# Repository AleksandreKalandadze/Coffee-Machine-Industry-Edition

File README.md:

# Coffee-Machine-Industry-Edition
Coffee Machine Industry Edition

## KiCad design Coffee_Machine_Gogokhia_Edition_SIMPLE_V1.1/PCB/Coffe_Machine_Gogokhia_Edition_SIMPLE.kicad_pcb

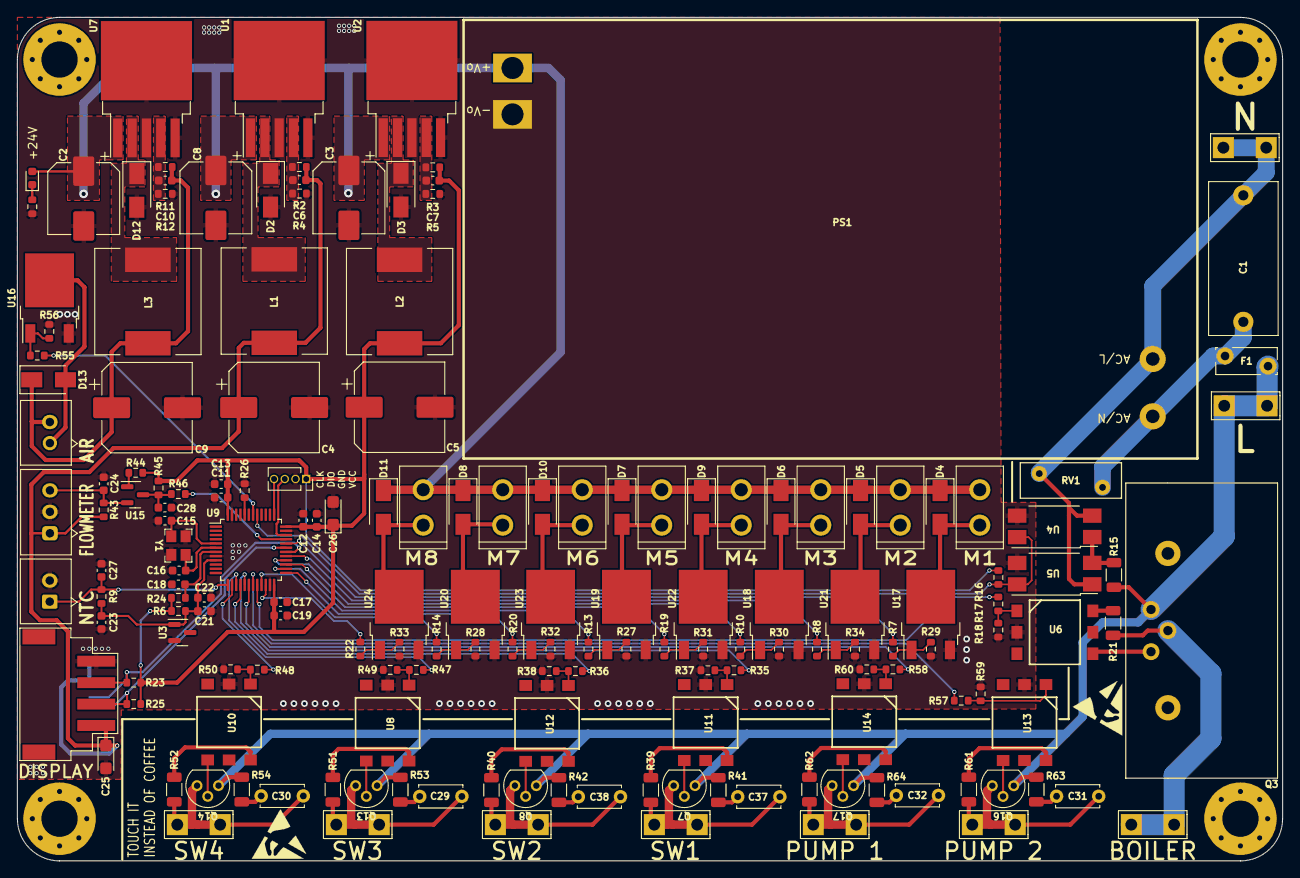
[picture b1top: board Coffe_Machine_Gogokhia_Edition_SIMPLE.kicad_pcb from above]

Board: 2 copper layers, 150.0 x 100.0 mm, 171 parts (1 on the bottom side), 99 nets.

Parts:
C1: 0.22uF; C_Rect_L18.0mm_W8.0mm_P15.00mm_FKS3_FKP3
C2, C3, C8: 100uF; CP_Elec_8x10
C4, C5, C9: 1000uF; CP_Elec_10x10.5
C6, C7, C10: 15nF; C_0603_1608Metric
C11, C13, C17, C18, C21, C22: .1uF; C_0603_1608Metric
C12, C14, C19, C23, C27: .01uF; C_0603_1608Metric
C15, C16: 22pF; C_0603_1608Metric
C24, C28: 0.1uF; C_0603_1608Metric
C25, C26: 100uF; CP_EIA-3216-10_Kemet-I
C29, C30, C31, C32, C37, C38: .01uF; C_Disc_D5.0mm_W2.5mm_P5.00mm
D1: LED; LED_0603_1608Metric
D2, D3, D12: SS34; D_SMA
D4, D5, D6, D7, D8, D9, D10, D11, D13: D; D_SMA
F1: Fuse; Fuse_Bourns_MF-RG300
J1: NEUT_TAB; TAB_Conn
J2: LINE_TAB; TAB_Conn
J3, J4, J6, J8, J10, J13, J16, J17: Conn_01x02; Molex_White_4_2mm_2P
J5: NTC; JST_2.54_2P
J7: JST_3P_2.54mm; JST_2.54_3P
J9: BOILER_TAB; TAB_Conn
J11: SW; PinSocket_1x04_P1.27mm_Vertical
J12: SW3_TAB; TAB_Conn
J14: SW1_TAB; TAB_Conn
J15: SW2_TAB; TAB_Conn
J18: Conn_01x10; FCC_1.0mm_10P
J19: SW; XH2.54_4P_SMD
J20: SW4_TAB; TAB_Conn
J21: Conn_01x02; JST_2.54_2P
J22: PUMP1_TAB; TAB_Conn
J23: PUMP2_TAB; TAB_Conn
L1, L2, L3: 47uH; L_12x12mm_H8mm
PS1: HLK-PM01; IRM-90-24
Q3: BTA16; BTA16_wH_SINK
Q7, Q8, Q13, Q14, Q16, Q17: BT131
R1: 4.1K; R_0603_1608Metric
R2: 3K; R_0603_1608Metric
R3: 1.6K; R_0603_1608Metric
R4, R5, R7, R8, R10, R13, R14, R19, R20, R22, R55: 1K; R_0603_1608Metric
R6: 33R; R_0603_1608Metric
R9: 100K; R_0603_1608Metric
R11: 11K; R_0603_1608Metric
R12: 1.2K; R_0603_1608Metric
R15: 100K; R_1206_3216Metric
R16, R18, R24, R26, R27, R28, R29, R30, R31, R32, R33, R34, R37, R38, R49, R50, R56, R59, R60: 10K; R_0603_1608Metric
R17, R35, R36, R47, R48, R57, R58: 330R; R_0603_1608Metric
R21, R39, R40, R51, R52, R61, R62: 180R; R_1206_3216Metric
R23, R25: R; R_0603_1608Metric
R41, R42, R53, R54, R63, R64: 39R; R_1206_3216Metric
R43, R45: 10k; R_0603_1608Metric
R44, R46: 1k; R_0603_1608Metric
RV1: Varistor; RV_Disc_D12mm_W4.2mm_P7.5mm
U1, U2, U7: LM2596T-ADJ; TO-263-5_TabPin3
U3: LM4040DBZ-3; SOT-23
U4, U5: PC817
U6, U8, U10, U11, U12, U13, U14: MOC3021M; DIP6_SMD
U9: STM32F103C8Tx; LQFP-48_7x7mm_P0.5mm
U15: MMBT2222; SOT-23
U16, U17, U18, U19, U20, U21, U22, U23, U24: 025C06C; TO-252-2
Y1: Crystal_GND24; Crystal_smd_3225

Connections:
+3V0: C21.1, C22.1, C23.1, R6.1, R9.1, U3.1 (K), U9.9 (VDDA)
+3V3: C5.1, C7.2, C11.1, C12.1, C13.1, C14.1, C17.1, C19.1, C26.1, J11.1, L2.2, R3.1, R6.2, R16.2, R23.2, R24.1, R25.2, R44.1, R45.1, U9.24 (VDD), U9.36 (VDD), U9.48 (VDD)
+5V: C4.1, C6.2, C25.1, J7.1, J18.1, J18.2, J18.3, J19.1, L1.2, R2.1, R43.1
+12V: C9.1, C10.2, D13.1 (K), J21.2, L3.2, R11.1
+24V: C2.1, C3.1, C8.1, D1.2 (A), D4.1 (K), D5.1 (K), D6.1 (K), D7.1 (K), D8.1 (K), D9.1 (K), D10.1 (K), D11.1 (K), J3.2, J4.2, J6.2, J8.2, J10.2, J13.2, J16.2, J17.2, PS1.4 (+Vout), U1.1 (VIN), U2.1 (VIN), U7.1 (VIN)
AIR_PUMP_uC: R55.1, U9.42 (PB6)
BOILER_uC: R17.2, U9.20 (PB2)
FLOWMETER: R46.2, U9.33 (PA12)
GND: C2.2, C3.2, C4.2, C5.2, C8.2, C9.2, C11.2, C12.2, C13.2, C14.2, C15.1, C16.1, C17.2, C18.1, C19.2, C21.2, C22.2, C23.2, C24.1, C25.2, C26.2, C27.2, C28.1, D2.2 (A), D3.2 (A), D12.2 (A), J5.2, J7.2, J11.2, J18.8, J18.9, J18.10, J19.4, PS1.3 (-Vout), R1.1, R4.2, R5.2, R12.2, R18.1, R26.1, R27.2, R28.2, R29.2, R30.2, R31.2, R32.2, R33.2, R34.2, R37.1, R38.1, R49.1, R50.1, R56.2, R59.1, R60.1, U1.3 (GND), U1.5 (~ON/OFF), U2.3 (GND), U2.5 (~ON/OFF), U3.2 (A), U4.3, U5.3, U6.2, U7.3 (GND), U7.5 (~ON/OFF), U8.2, U9.8 (VSSA), U9.23 (VSS), U9.35 (VSS), U9.47 (VSS), U10.2, U11.2, U12.2, U13.2, U14.2, U16.3 (S), U17.3 (S), U18.3 (S), U19.3 (S), U20.3 (S), U21.3 (S), U22.3 (S), U23.3 (S), U24.3 (S), Y1.2, Y1.4
LINE: F1.1, J2.1, Q3.1 (A1), Q7.1 (A1), Q8.1 (A1), Q13.1 (A1), Q14.1 (A1), Q16.1 (A1), Q17.1 (A1), R15.2, R41.1, R42.1, R53.1, R54.1, R63.1, R64.1
Motor_1: R7.1, U9.32 (PA11)
Motor_2: R8.1, U9.29 (PA8)
Motor_3: R10.1, U9.28 (PB15)
Motor_4: R19.1, U9.27 (PB14)
Motor_5: R13.1, U9.26 (PB13)
Motor_6: R20.1, U9.25 (PB12)
Motor_7: R14.1, U9.21 (PB10)
Motor_8: R22.1, U9.22 (PB11)
NEUT: C1.1, J1.1, PS1.2 (AC/N), RV1.2, U4.2, U5.1
NTC: C27.1, J5.1, R9.2, U9.13 (PA3)
unnamed: C1.2, F1.2, PS1.1 (AC/L), RV1.1
unnamed: C6.1, R2.2, R4.1, U1.4 (FB)
unnamed: C7.1, R3.2, R5.1, U2.4 (FB)
unnamed: C10.1, R11.2, R12.1, U7.4 (FB)
unnamed: C15.2, U9.5 (PD0), Y1.1
unnamed: C16.2, U9.6 (PD1), Y1.3
unnamed: C18.2, R24.2, U9.7 (NRST)
unnamed: C24.2, J7.3, R43.2, U15.2 (E)
unnamed: C28.2, R45.2, R46.1, U15.3 (C)
unnamed: C29.1, J12.1, Q13.2 (A2), R51.1
unnamed: C29.2, R53.2
unnamed: C30.1, J20.1, Q14.2 (A2), R52.1
unnamed: C30.2, R54.2
unnamed: C31.1, J22.1, Q16.2 (A2), R61.1
unnamed: C31.2, R63.2
unnamed: C32.1, J23.1, Q17.2 (A2), R62.1
unnamed: C32.2, R64.2
unnamed: C37.1, J14.1, Q7.2 (A2), R39.1
unnamed: C37.2, R41.2
unnamed: C38.1, J15.1, Q8.2 (A2), R40.1
unnamed: C38.2, R42.2
unnamed: D1.1 (K), R1.2
unnamed: D2.1 (K), L1.1, U1.2 (OUT)
unnamed: D3.1 (K), L2.1, U2.2 (OUT)
unnamed: D4.2 (A), J3.1, U17.2 (D)
unnamed: D5.2 (A), J4.1, U21.2 (D)
unnamed: D6.2 (A), J6.1, U18.2 (D)
unnamed: D7.2 (A), J8.1, U19.2 (D)
unnamed: D8.2 (A), J10.1, U20.2 (D)
unnamed: D9.2 (A), J13.1, U22.2 (D)
unnamed: D10.2 (A), J16.1, U23.2 (D)
unnamed: D11.2 (A), J17.1, U24.2 (D)
unnamed: D12.1 (K), L3.1, U7.2 (OUT)
unnamed: D13.2 (A), J21.1, U16.2 (D)
unnamed: J9.1, Q3.2 (A2), R21.1
unnamed: Q3.3 (G), U6.4
unnamed: Q7.3 (G), U11.4
unnamed: Q8.3 (G), U12.4
unnamed: Q13.3 (G), U8.4
unnamed: Q14.3 (G), U10.4
unnamed: Q16.3 (G), U13.4
unnamed: Q17.3 (G), U14.4
unnamed: R10.2, R30.1, U18.1 (G)
unnamed: R13.2, R27.1, U19.1 (G)
unnamed: R14.2, R28.1, U20.1 (G)
unnamed: R15.1, U4.1, U5.2
unnamed: R17.1, R18.2, U6.1
unnamed: R19.2, R31.1, U22.1 (G)
unnamed: R20.2, R32.1, U23.1 (G)
unnamed: R21.2, U6.6
unnamed: R22.2, R33.1, U24.1 (G)
unnamed: R26.2, U9.44 (BOOT0)
unnamed: R7.2, R29.1, U17.1 (G)
unnamed: R8.2, R34.1, U21.1 (G)
unnamed: R35.1, R37.2, U11.1
unnamed: R36.1, R38.2, U12.1
unnamed: R39.2, U11.6
unnamed: R40.2, U12.6
unnamed: R44.2, U15.1 (B)
unnamed: R47.1, R49.2, U8.1
unnamed: R48.1, R50.2, U10.1
unnamed: R51.2, U8.6
unnamed: R52.2, U10.6
unnamed: R55.2, R56.1, U16.1 (G)
unnamed: R57.1, R59.2, U13.1
unnamed: R58.1, R60.2, U14.1
unnamed: R61.2, U13.6
unnamed: R62.2, U14.6
PUMP1_uC: R57.2, U9.19 (PB1)
PUMP2_uC: R58.2, U9.18 (PB0)
SW1_uC: R35.2, U9.17 (PA7)
SW2_uC: R36.2, U9.16 (PA6)
SW3_uC: R47.2, U9.15 (PA5)
SW4_uC: R48.2, U9.14 (PA4)
SWCLK: J11.4, U9.37 (PA14)
SWDIO: J11.3, U9.34 (PA13)
UART_Rx: J18.6, J19.2, R25.1, U9.31 (PA10)
UART_Tx: J18.5, J19.3, R23.1, U9.30 (PA9)
Z_CROSS: R16.1, U4.4, U5.4, U9.41 (PB5)

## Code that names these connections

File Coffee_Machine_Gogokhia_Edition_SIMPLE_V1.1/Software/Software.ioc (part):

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Mcu.Name=STM32F103C(8-B)Tx
Mcu.Package=LQFP48
Mcu.UserName=STM32F103C8Tx
PA10.Mode=Asynchronous
PA10.Signal=USART1_RX
PA12.GPIOParameters=GPIO_Label
PA12.GPIO_Label=FLOWMETER
PA12.Signal=GPXTI12
PA13.Mode=Serial_Wire
PA13.Signal=SYS_JTMS-SWDIO
PA14.Mode=Serial_Wire
PA14.Signal=SYS_JTCK-SWCLK
PA3.GPIOParameters=GPIO_Label
PA3.GPIO_Label=NTC
PA3.Signal=ADCx_IN3
PA9.Mode=Asynchronous
PA9.Signal=USART1_TX
PB5.GPIOParameters=GPIO_Label
PB5.GPIO_Label=ZERO CROSS
PB5.Signal=GPXTI5
PB6.GPIOParameters=GPIO_Label
PB6.GPIO_Label=AIR_PUMP
PB6.Signal=GPIO_Output
PD0-OSC_IN.Mode=HSE-External-Oscillator
PD0-OSC_IN.Signal=RCC_OSC_IN
PD1-OSC_OUT.Mode=HSE-External-Oscillator
PD1-OSC_OUT.Signal=RCC_OSC_OUT
RCC.SYSCLKFreq_VALUE=72000000
RCC.SYSCLKSource=RCC_SYSCLKSOURCE_PLLCLK
board=custom

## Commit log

2022-03-16 uptade
2022-03-23 Edited
2022-03-30 gerber
2022-04-29 Revision
2022-04-29 Revert "1"
